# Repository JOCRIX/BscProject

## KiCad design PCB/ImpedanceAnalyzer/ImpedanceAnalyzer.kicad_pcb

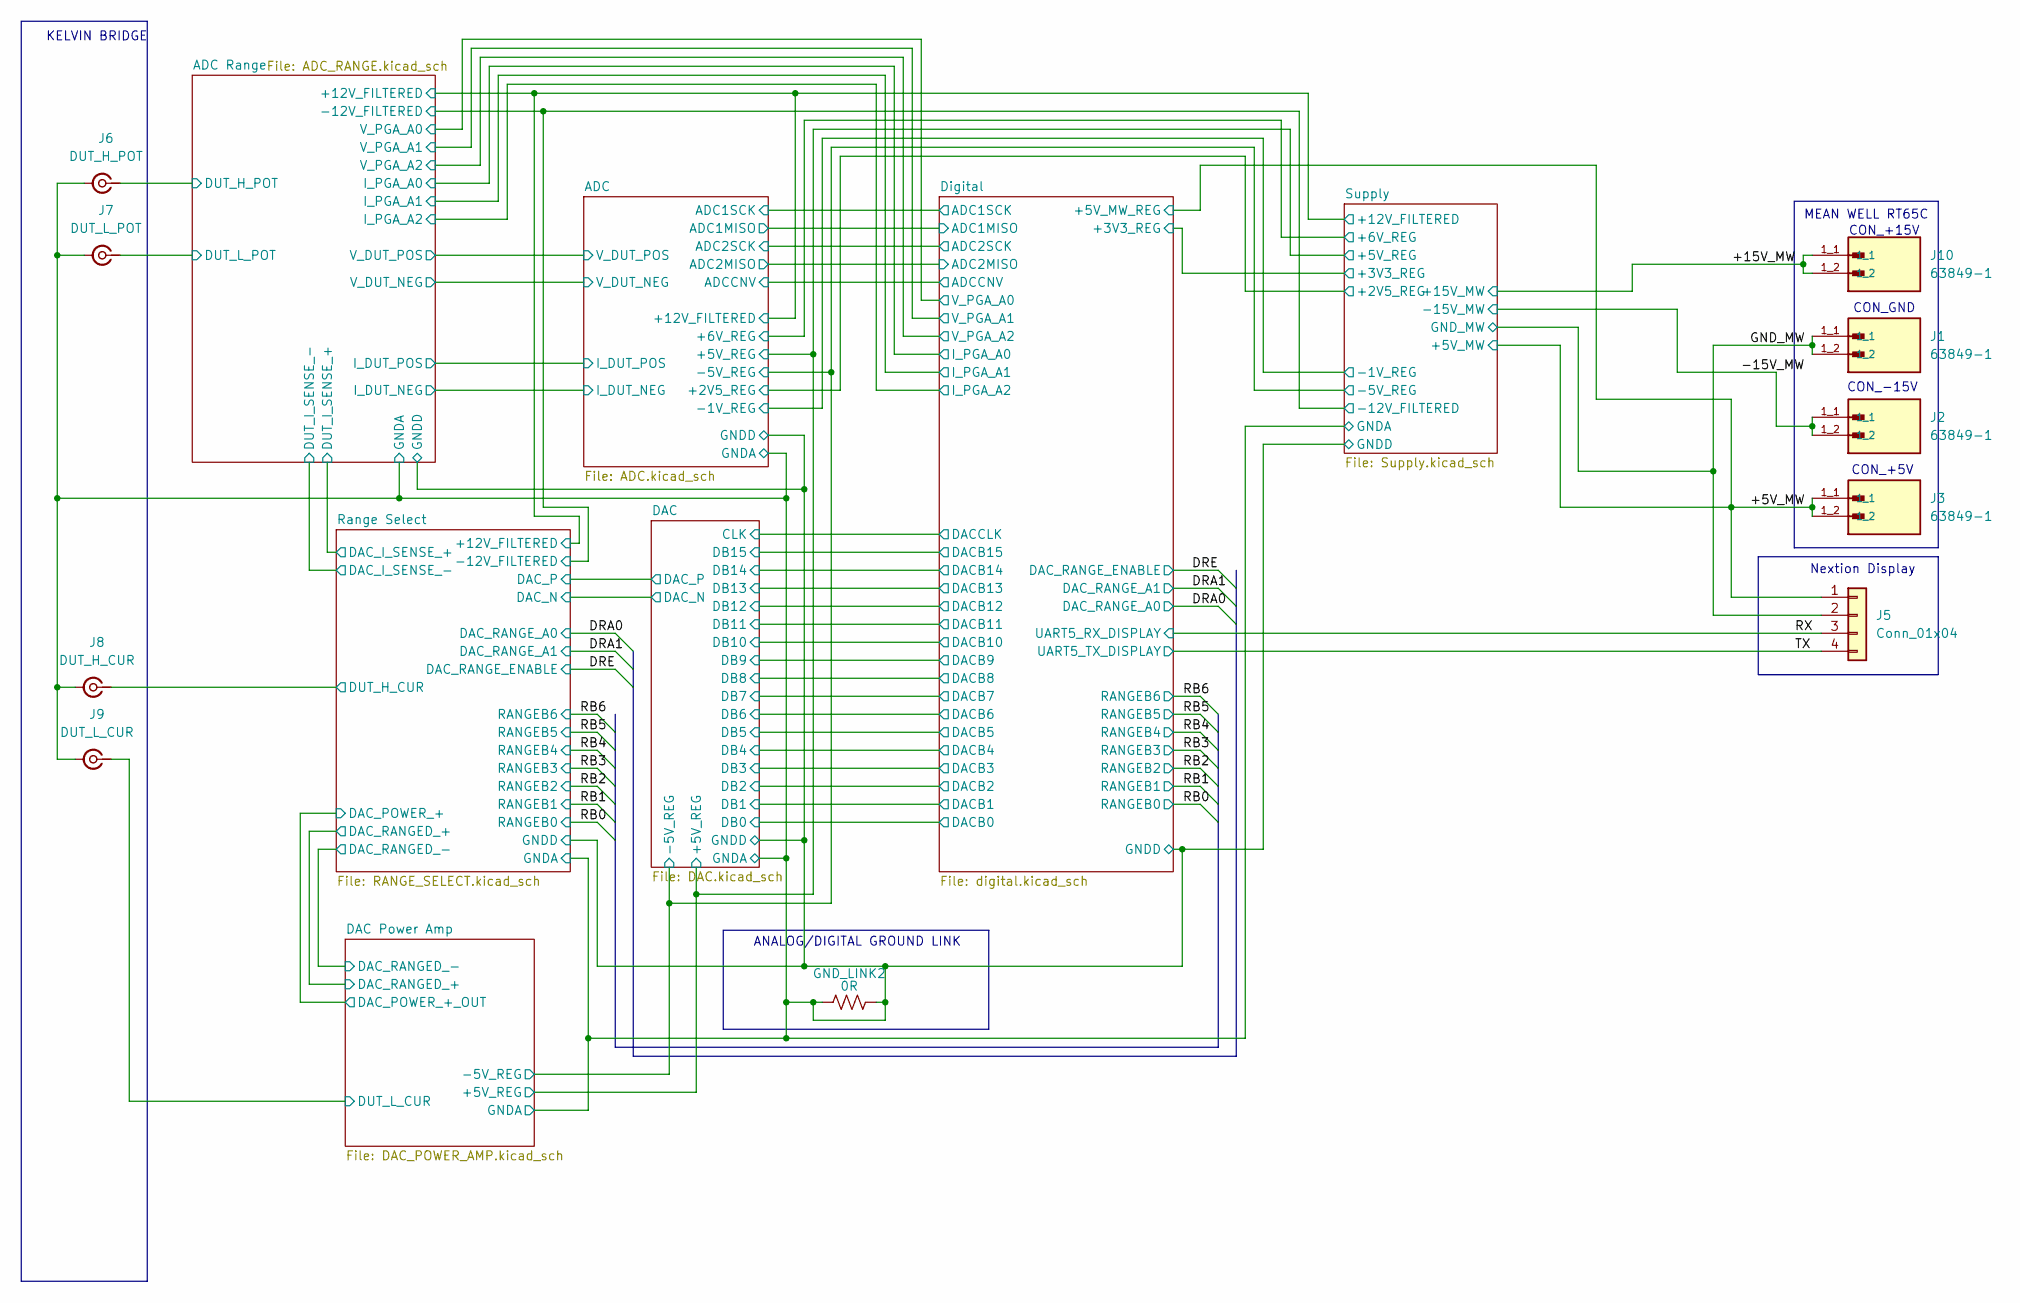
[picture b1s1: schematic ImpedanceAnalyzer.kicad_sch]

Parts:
GND_LINK2: 0R; Resistor SMD - 2818
J1, J2, J3, J10: 63849-1; TE_63849-1
J5: Conn_01x04; JST_XH_B4B-XH-A_1x04_P2.50mm_Vertical
J6: DUT_H_POT; BNC_TEConnectivity_1478204_Vertical
J7: DUT_L_POT; BNC_TEConnectivity_1478204_Vertical
J8: DUT_H_CUR; BNC_TEConnectivity_1478204_Vertical
J9: DUT_L_CUR; BNC_TEConnectivity_1478204_Vertical

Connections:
/+5V_MW: J3.1_1, J3.1_2, J5.1; also elsewhere on the board
/+15V_MW: J10.1_1, J10.1_2; also elsewhere on the board
/-15V_MW: J2.1_1, J2.1_2; also elsewhere on the board
/ADC Range/DUT_H_POT: J6.1 (In); also elsewhere on the board
/ADC Range/DUT_I_SENSE_-: J8.1 (In); also elsewhere on the board
/ADC Range/DUT_L_POT: J7.1 (In); also elsewhere on the board
/DAC Power Amp/DUT_L_CUR: J9.1 (In); also elsewhere on the board
/GND_MW: J1.1_1, J1.1_2, J5.2; also elsewhere on the board
/RX: J5.3; also elsewhere on the board
/TX: J5.4; also elsewhere on the board

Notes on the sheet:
KELVIN BRIDGE
CON_+15V
MEAN WELL RT65C
CON_GND
Nextion Display
CON_+5V
CON_-15V
ANALOG/DIGITAL GROUND LINK

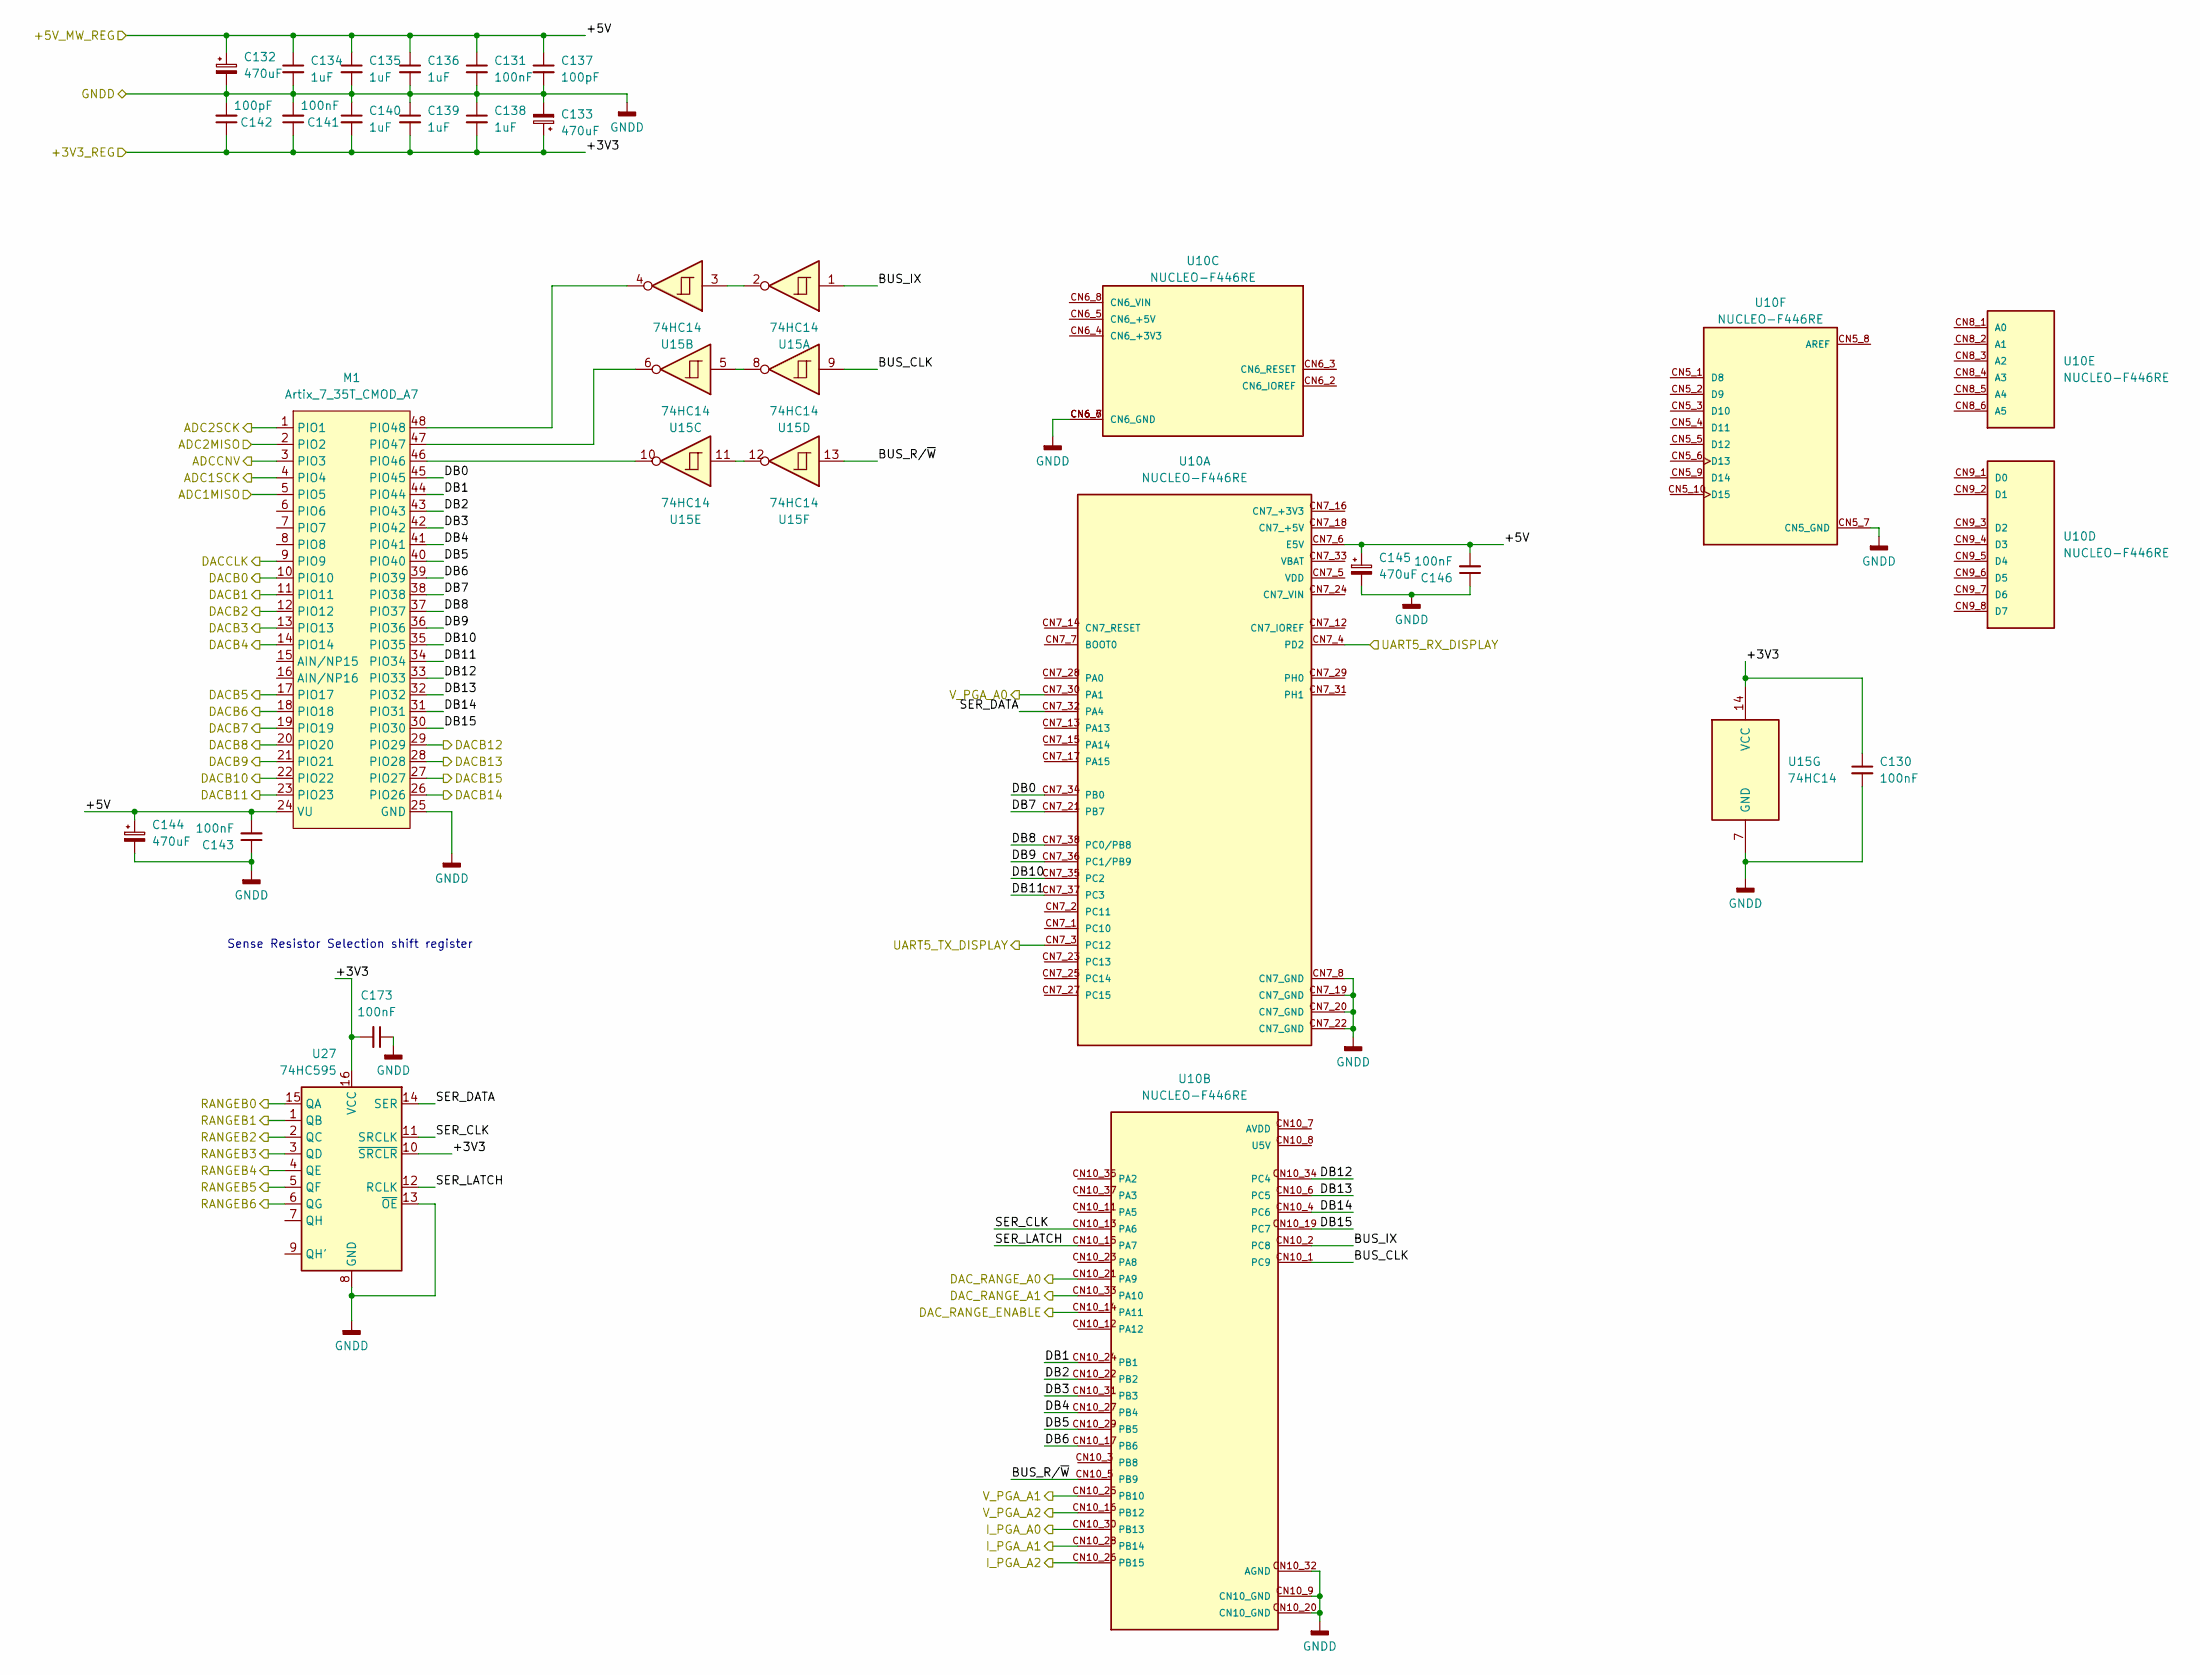
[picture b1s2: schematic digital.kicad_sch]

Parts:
C130, C131, C141, C143, C146, C173: 100nF; C_0805_2012Metric_Pad1.18x1.45mm_HandSolder
C132, C133, C144, C145: 470uF; CP_Radial_D10.0mm_P5.00mm
C134, C135, C136, C138, C139, C140: 1uF; C_0805_2012Metric_Pad1.18x1.45mm_HandSolder
C137, C142: 100pF; C_Disc_D3.4mm_W2.1mm_P2.50mm
M1: Artix_7_35T_CMOD_A7; CMOD A7 Module
U10: NUCLEO-F446RE; MODULE_NUCLEO-F446RE; PARTREV 13
U15: 74HC14; DIP-14_W7.62mm
U27: 74HC595; DIP-16_W7.62mm

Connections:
/+5V_MW: C131.1, C132.1, C134.1, C135.1, C136.1, C137.1, C143.2, C144.1, C145.1, C146.2, M1.24 (VU), U10.CN7_6 (E5V); also elsewhere on the board
/ADC Range/I_PGA_A0: U10.CN10_30 (PB13); also elsewhere on the board
/ADC Range/I_PGA_A1: U10.CN10_28 (PB14); also elsewhere on the board
/ADC Range/I_PGA_A2: U10.CN10_26 (PB15); also elsewhere on the board
/ADC Range/V_PGA_A0: U10.CN7_30 (PA1); also elsewhere on the board
/ADC Range/V_PGA_A1: U10.CN10_25 (PB10); also elsewhere on the board
/ADC Range/V_PGA_A2: U10.CN10_16 (PB12); also elsewhere on the board
/ADC/ADC1MISO: M1.5 (PIO5); also elsewhere on the board
/ADC/ADC1SCK: M1.4 (PIO4); also elsewhere on the board
/ADC/ADC2MISO: M1.2 (PIO2); also elsewhere on the board
/ADC/ADC2SCK: M1.1 (PIO1); also elsewhere on the board
/ADC/ADCCNV: M1.3 (PIO3); also elsewhere on the board
/DAC/CLK: M1.9 (PIO9); also elsewhere on the board
/DAC/DB0: M1.10 (PIO10); also elsewhere on the board
/DAC/DB1: M1.11 (PIO11); also elsewhere on the board
/DAC/DB2: M1.12 (PIO12); also elsewhere on the board
/DAC/DB3: M1.13 (PIO13); also elsewhere on the board
/DAC/DB4: M1.14 (PIO14); also elsewhere on the board
/DAC/DB5: M1.17 (PIO17); also elsewhere on the board
/DAC/DB6: M1.18 (PIO18); also elsewhere on the board
/DAC/DB7: M1.19 (PIO19); also elsewhere on the board
/DAC/DB8: M1.20 (PIO20); also elsewhere on the board
/DAC/DB9: M1.21 (PIO21); also elsewhere on the board
/DAC/DB10: M1.22 (PIO22); also elsewhere on the board
/DAC/DB11: M1.23 (PIO23); also elsewhere on the board
/DAC/DB12: M1.29 (PIO29); also elsewhere on the board
/DAC/DB13: M1.28 (PIO28); also elsewhere on the board
/DAC/DB14: M1.26 (PIO26); also elsewhere on the board
/DAC/DB15: M1.27 (PIO27); also elsewhere on the board
/DRA0: U10.CN10_21 (PA9); also elsewhere on the board
/DRA1: U10.CN10_33 (PA10); also elsewhere on the board
/DRE: U10.CN10_14 (PA11); also elsewhere on the board
/Digital/+3V3: C130.1, C133.1, C138.2, C139.2, C140.2, C141.1, C142.1, C173.2, U15.14 (VCC), U27.10 (~SRCLR), U27.16 (VCC); also elsewhere on the board
/Digital/BUS_CLK: U10.CN10_1 (PC9), U15.9
/Digital/BUS_IX: U10.CN10_2 (PC8), U15.1
/Digital/BUS_R/~W: U10.CN10_5 (PB9), U15.13
/Digital/DB0: M1.45 (PIO45), U10.CN7_34 (PB0)
/Digital/DB1: M1.44 (PIO44), U10.CN10_24 (PB1)
/Digital/DB2: M1.43 (PIO43), U10.CN10_22 (PB2)
/Digital/DB3: M1.42 (PIO42), U10.CN10_31 (PB3)
/Digital/DB4: M1.41 (PIO41), U10.CN10_27 (PB4)
/Digital/DB5: M1.40 (PIO40), U10.CN10_29 (PB5)
/Digital/DB6: M1.39 (PIO39), U10.CN10_17 (PB6)
/Digital/DB7: M1.38 (PIO38), U10.CN7_21 (PB7)
/Digital/DB8: M1.37 (PIO37), U10.CN7_38 (PC0/PB8)
/Digital/DB9: M1.36 (PIO36), U10.CN7_36 (PC1/PB9)
/Digital/DB10: M1.35 (PIO35), U10.CN7_35 (PC2)
/Digital/DB11: M1.34 (PIO34), U10.CN7_37 (PC3)
/Digital/DB12: M1.33 (PIO33), U10.CN10_34 (PC4)
/Digital/DB13: M1.32 (PIO32), U10.CN10_6 (PC5)
/Digital/DB14: M1.31 (PIO31), U10.CN10_4 (PC6)
/Digital/DB15: M1.30 (PIO30), U10.CN10_19 (PC7)
/Digital/SER_CLK: U10.CN10_13 (PA6), U27.11 (SRCLK)
/Digital/SER_DATA: U10.CN7_32 (PA4), U27.14 (SER)
/Digital/SER_LATCH: U10.CN10_15 (PA7), U27.12 (RCLK)
/RB0: U27.15 (QA); also elsewhere on the board
/RB1: U27.1 (QB); also elsewhere on the board
/RB2: U27.2 (QC); also elsewhere on the board
/RB3: U27.3 (QD); also elsewhere on the board
/RB4: U27.4 (QE); also elsewhere on the board
/RB5: U27.5 (QF); also elsewhere on the board
/RB6: U27.6 (QG); also elsewhere on the board
/RX: U10.CN7_4 (PD2); also elsewhere on the board
/TX: U10.CN7_3 (PC12); also elsewhere on the board
unnamed: M1.46 (PIO46), U15.10
unnamed: M1.47 (PIO47), U15.6
unnamed: M1.48 (PIO48), U15.4
unnamed: U15.2, U15.3
unnamed: U15.5, U15.8
unnamed: U15.11, U15.12

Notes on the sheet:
Sense Resistor Selection shift register

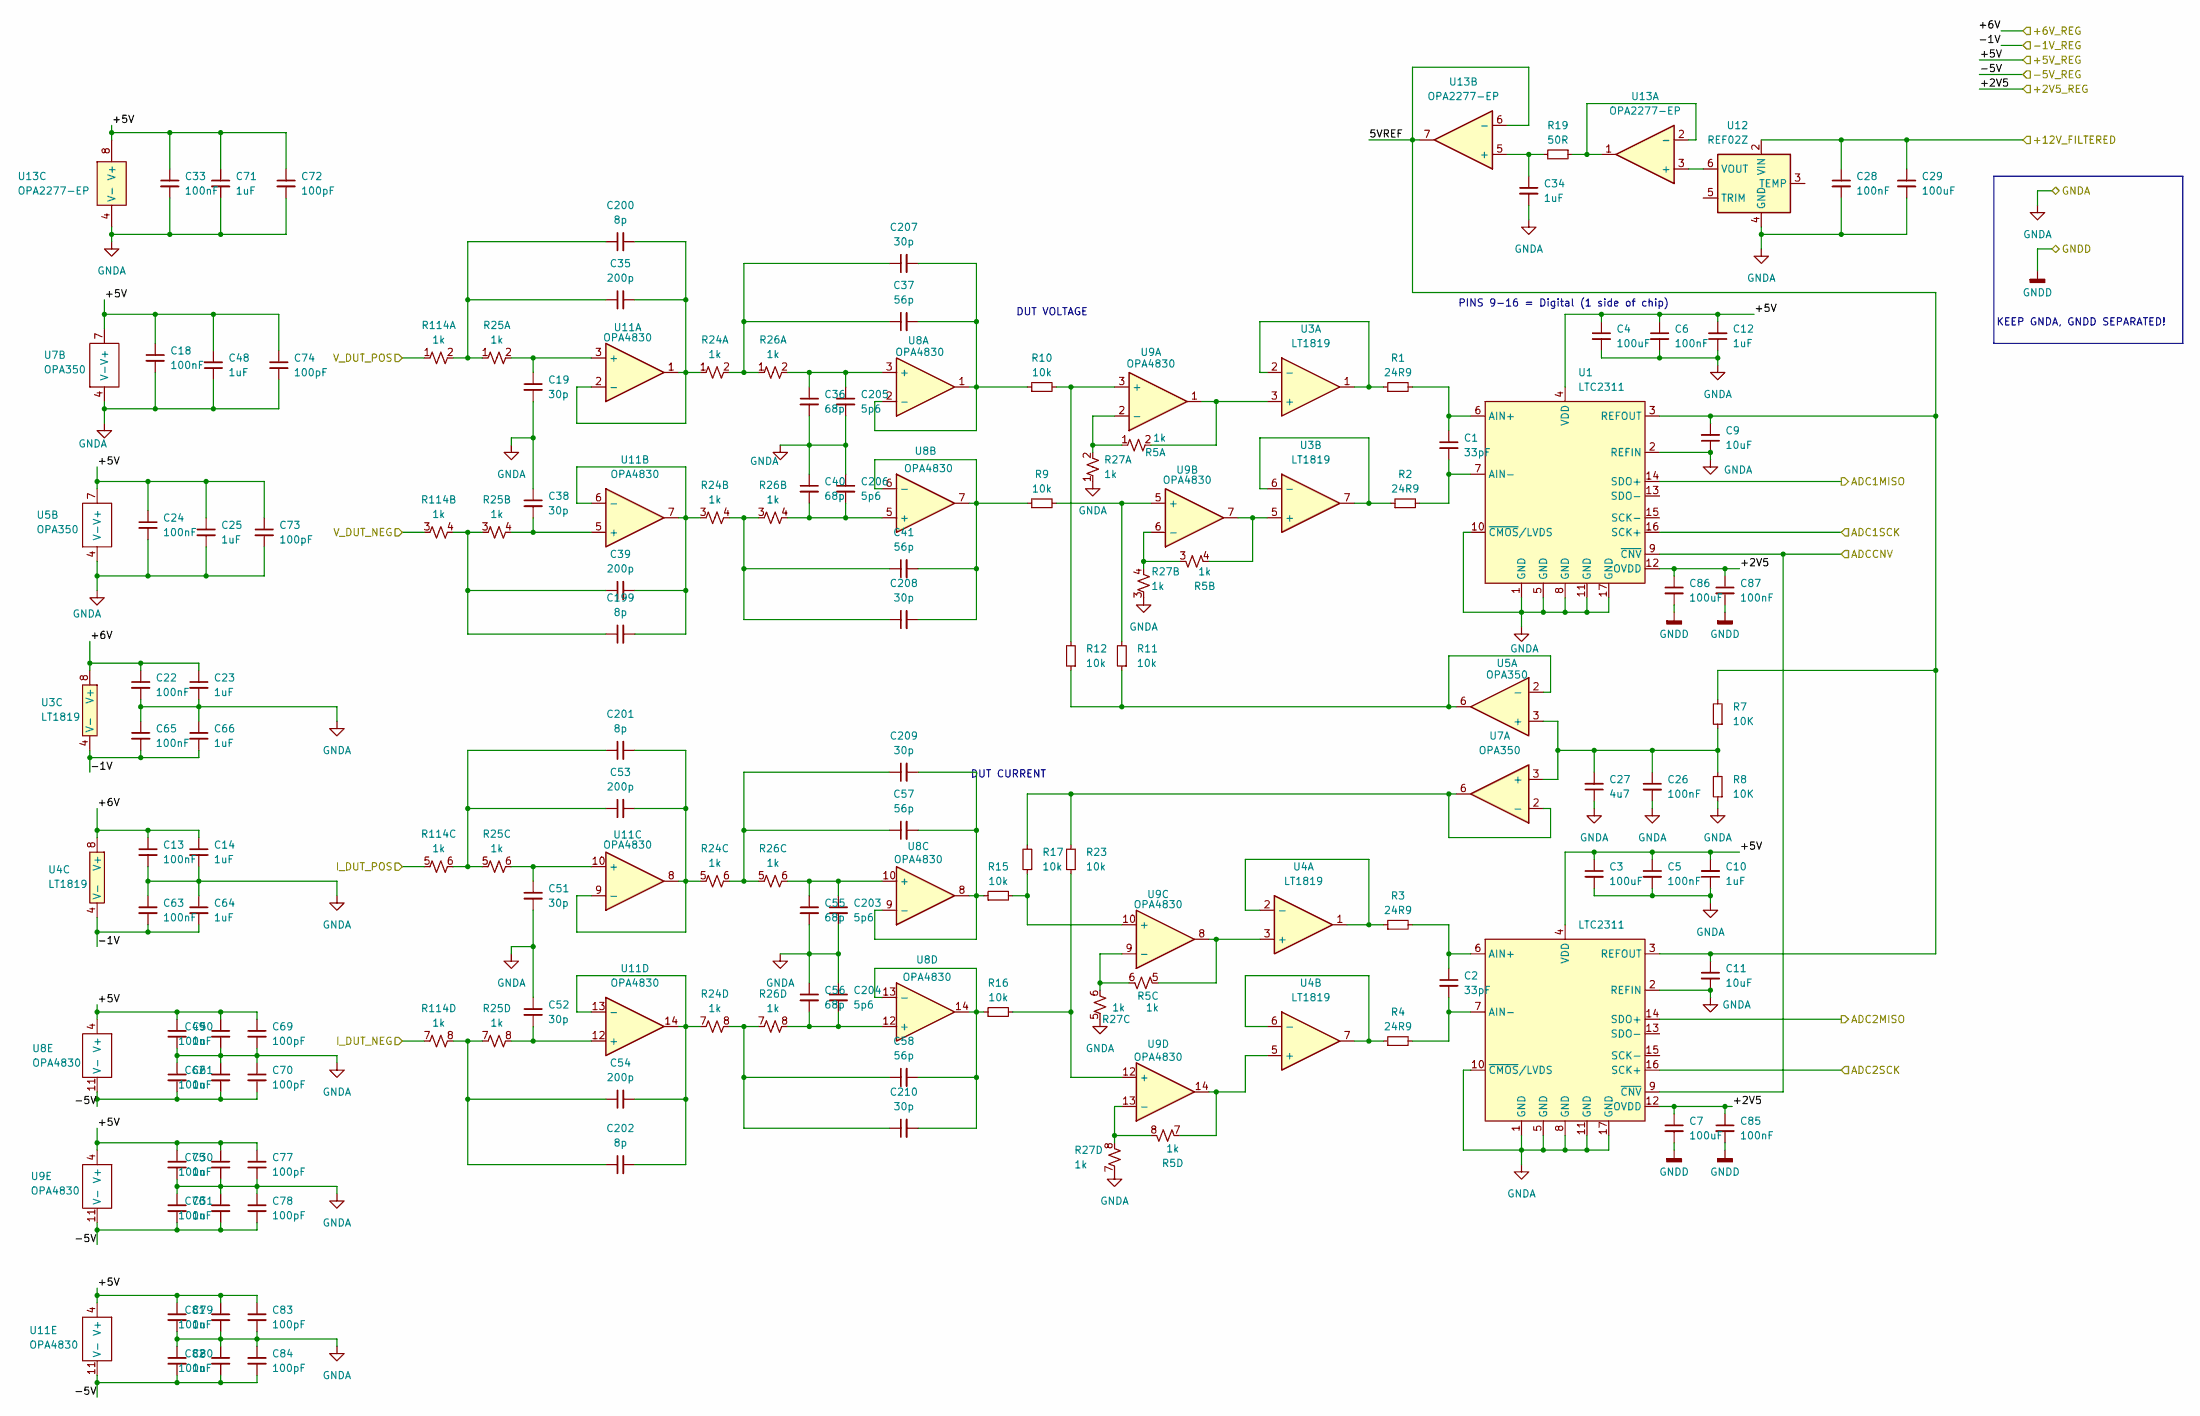
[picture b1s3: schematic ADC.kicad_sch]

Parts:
C1, C2: 33pF; C_0805_2012Metric_Pad1.18x1.45mm_HandSolder
C3, C4, C7, C29, C86: 100uF; C_1206_3216Metric_Pad1.33x1.80mm_HandSolder
C5, C6, C13, C18, C22, C24, C26, C28, C33, C63, C65, C85, C87: 100nF; C_0805_2012Metric_Pad1.18x1.45mm_HandSolder
C9, C11: 10uF; C_1206_3216Metric_Pad1.33x1.80mm_HandSolder
C10, C12, C14, C23, C25, C30, C31, C34, C48, C50, C61, C64, C66, C71, C79, C80: 1uF; C_0805_2012Metric_Pad1.18x1.45mm_HandSolder
C19, C38, C51, C52, C207, C208, C209, C210: 30p; C_0603_1608Metric_Pad1.08x0.95mm_HandSolder
C27: 4u7; C_1206_3216Metric_Pad1.33x1.80mm_HandSolder
C35, C39, C53, C54: 200p; C_0603_1608Metric_Pad1.08x0.95mm_HandSolder
C36, C40, C55, C56: 68p; C_0603_1608Metric_Pad1.08x0.95mm_HandSolder
C37, C41, C57, C58: 56p; C_0603_1608Metric_Pad1.08x0.95mm_HandSolder
C49, C62, C75, C76, C81, C82: 100n; C_0805_2012Metric_Pad1.18x1.45mm_HandSolder
C69, C70, C72, C73, C74, C77, C78, C83, C84: 100pF; C_Disc_D3.4mm_W2.1mm_P2.50mm
C199, C200, C201, C202: 8p; C_0603_1608Metric_Pad1.08x0.95mm_HandSolder
C203, C204, C205, C206: 5p6; C_0603_1608Metric_Pad1.08x0.95mm_HandSolder
R1, R2, R3, R4: 24R9; R_0805_2012Metric_Pad1.20x1.40mm_HandSolder
R5, R24, R25, R26, R27, R114: 1k; R_Array_SIP8
R7, R8: 10K; R_0805_2012Metric_Pad1.20x1.40mm_HandSolder
R9, R10, R11, R12, R15, R16, R17, R23: 10k; R_0805_2012Metric_Pad1.20x1.40mm_HandSolder
R19: 50R; R_0805_2012Metric_Pad1.20x1.40mm_HandSolder
U1, U2: LTC2311; MSOP-16-1EP_3x4mm_P0.5mm_EP1.65x2.85mm_ThermalVias
U3, U4: LT1819; SOIC-8_3.9x4.9mm_P1.27mm
U5, U7: OPA350; DIP-8_W7.62mm
U8, U9, U11: OPA4830; TSSOP-14_4.4x5mm_P0.65mm
U12: REF02Z; DIP-8_W7.62mm
U13: OPA2277-EP; DIP-8_W7.62mm

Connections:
/ADC Range/+12V: C28.1, C29.1, U12.2 (VIN); also elsewhere on the board
/ADC Range/I_DUT_NEG: R114.7; also elsewhere on the board
/ADC Range/I_DUT_POS: R114.5; also elsewhere on the board
/ADC Range/V_DUT_NEG: R114.3; also elsewhere on the board
/ADC Range/V_DUT_POS: R114.1; also elsewhere on the board
/ADC/5VREF: C9.2, C11.1, R7.2, U1.3 (REFOUT), U2.3 (REFOUT), U13.6 (-), U13.7
/ADC/+2V5: C7.1, C85.1, C86.1, C87.1, U1.12 (OVDD), U2.12 (OVDD); also elsewhere on the board
/ADC/+6V: C13.1, C14.1, C22.1, C23.1, U3.8 (V+), U4.8 (V+); also elsewhere on the board
/ADC/-1V: C63.2, C64.2, C65.2, C66.2, U3.4 (V-), U4.4 (V-); also elsewhere on the board
/ADC/ADC1MISO: U1.14 (SDO+); also elsewhere on the board
/ADC/ADC1SCK: U1.16 (SCK+); also elsewhere on the board
/ADC/ADC2MISO: U2.14 (SDO+); also elsewhere on the board
/ADC/ADC2SCK: U2.16 (SCK+); also elsewhere on the board
/ADC/ADCCNV: U1.9 (~CNV), U2.9 (~CNV); also elsewhere on the board
unnamed: C39.1, C199.1, R25.3, R114.4
unnamed: C35.1, C200.1, R25.1, R114.2
unnamed: C53.1, C201.1, R25.5, R114.6
unnamed: C54.1, C202.1, R25.7, R114.8
unnamed: C37.1, C207.1, R24.2, R26.1
unnamed: C41.1, C208.1, R24.4, R26.3
unnamed: C57.1, C209.1, R24.6, R26.5
unnamed: C58.1, C210.1, R24.8, R26.7
unnamed: C1.1, R1.2, U1.6 (AIN+)
unnamed: C1.2, R2.2, U1.7 (AIN-)
unnamed: C2.1, R3.2, U2.6 (AIN+)
unnamed: C2.2, R4.2, U2.7 (AIN-)
unnamed: R5.2, U3.3 (+), U9.1
unnamed: R1.1, U3.1, U3.2 (-)
unnamed: R5.4, U3.5 (+), U9.7
unnamed: R2.1, U3.6 (-), U3.7
unnamed: R5.5, U4.3 (+), U9.8
unnamed: R3.1, U4.1, U4.2 (-)
unnamed: R5.7, U4.5 (+), U9.14
unnamed: R4.1, U4.6 (-), U4.7
unnamed: C26.1, C27.2, R7.1, R8.2, U5.3 (+), U7.3 (+)
unnamed: R11.1, R12.1, U5.2 (-), U5.6
unnamed: R17.2, R23.2, U7.2 (-), U7.6
unnamed: C36.1, C205.1, R26.2, U8.3 (+)
unnamed: C37.2, C207.2, R10.1, U8.1, U8.2 (-)
unnamed: C40.2, C206.2, R26.4, U8.5 (+)
unnamed: C41.2, C208.2, R9.1, U8.6 (-), U8.7
unnamed: C55.1, C203.1, R26.6, U8.10 (+)
unnamed: C57.2, C209.2, R15.1, U8.8, U8.9 (-)
unnamed: C56.2, C204.2, R26.8, U8.12 (+)
unnamed: C58.2, C210.2, R16.1, U8.13 (-), U8.14
unnamed: R10.2, R12.2, U9.3 (+)
unnamed: R5.1, R27.2, U9.2 (-)
unnamed: R9.2, R11.2, U9.5 (+)
unnamed: R5.3, R27.4, U9.6 (-)
unnamed: R15.2, R17.1, U9.10 (+)
unnamed: R5.6, R27.6, U9.9 (-)
unnamed: R16.2, R23.1, U9.12 (+)
unnamed: R5.8, R27.8, U9.13 (-)
unnamed: C19.1, R25.2, U11.3 (+)
unnamed: C35.2, C200.2, R24.1, U11.1, U11.2 (-)
unnamed: C38.2, R25.4, U11.5 (+)
unnamed: C39.2, C199.2, R24.3, U11.6 (-), U11.7
unnamed: C51.1, R25.6, U11.10 (+)
unnamed: C53.2, C201.2, R24.5, U11.8, U11.9 (-)
unnamed: C52.2, R25.8, U11.12 (+)
unnamed: C54.2, C202.2, R24.7, U11.13 (-), U11.14
unnamed: U12.6 (VOUT), U13.3 (+)
unnamed: R19.1, U13.1, U13.2 (-)
unnamed: C34.1, R19.2, U13.5 (+)

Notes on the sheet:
KEEP GNDA, GNDD SEPARATED!
DUT CURRENT
PINS 9-16 = Digital (1 side of chip)
DUT VOLTAGE

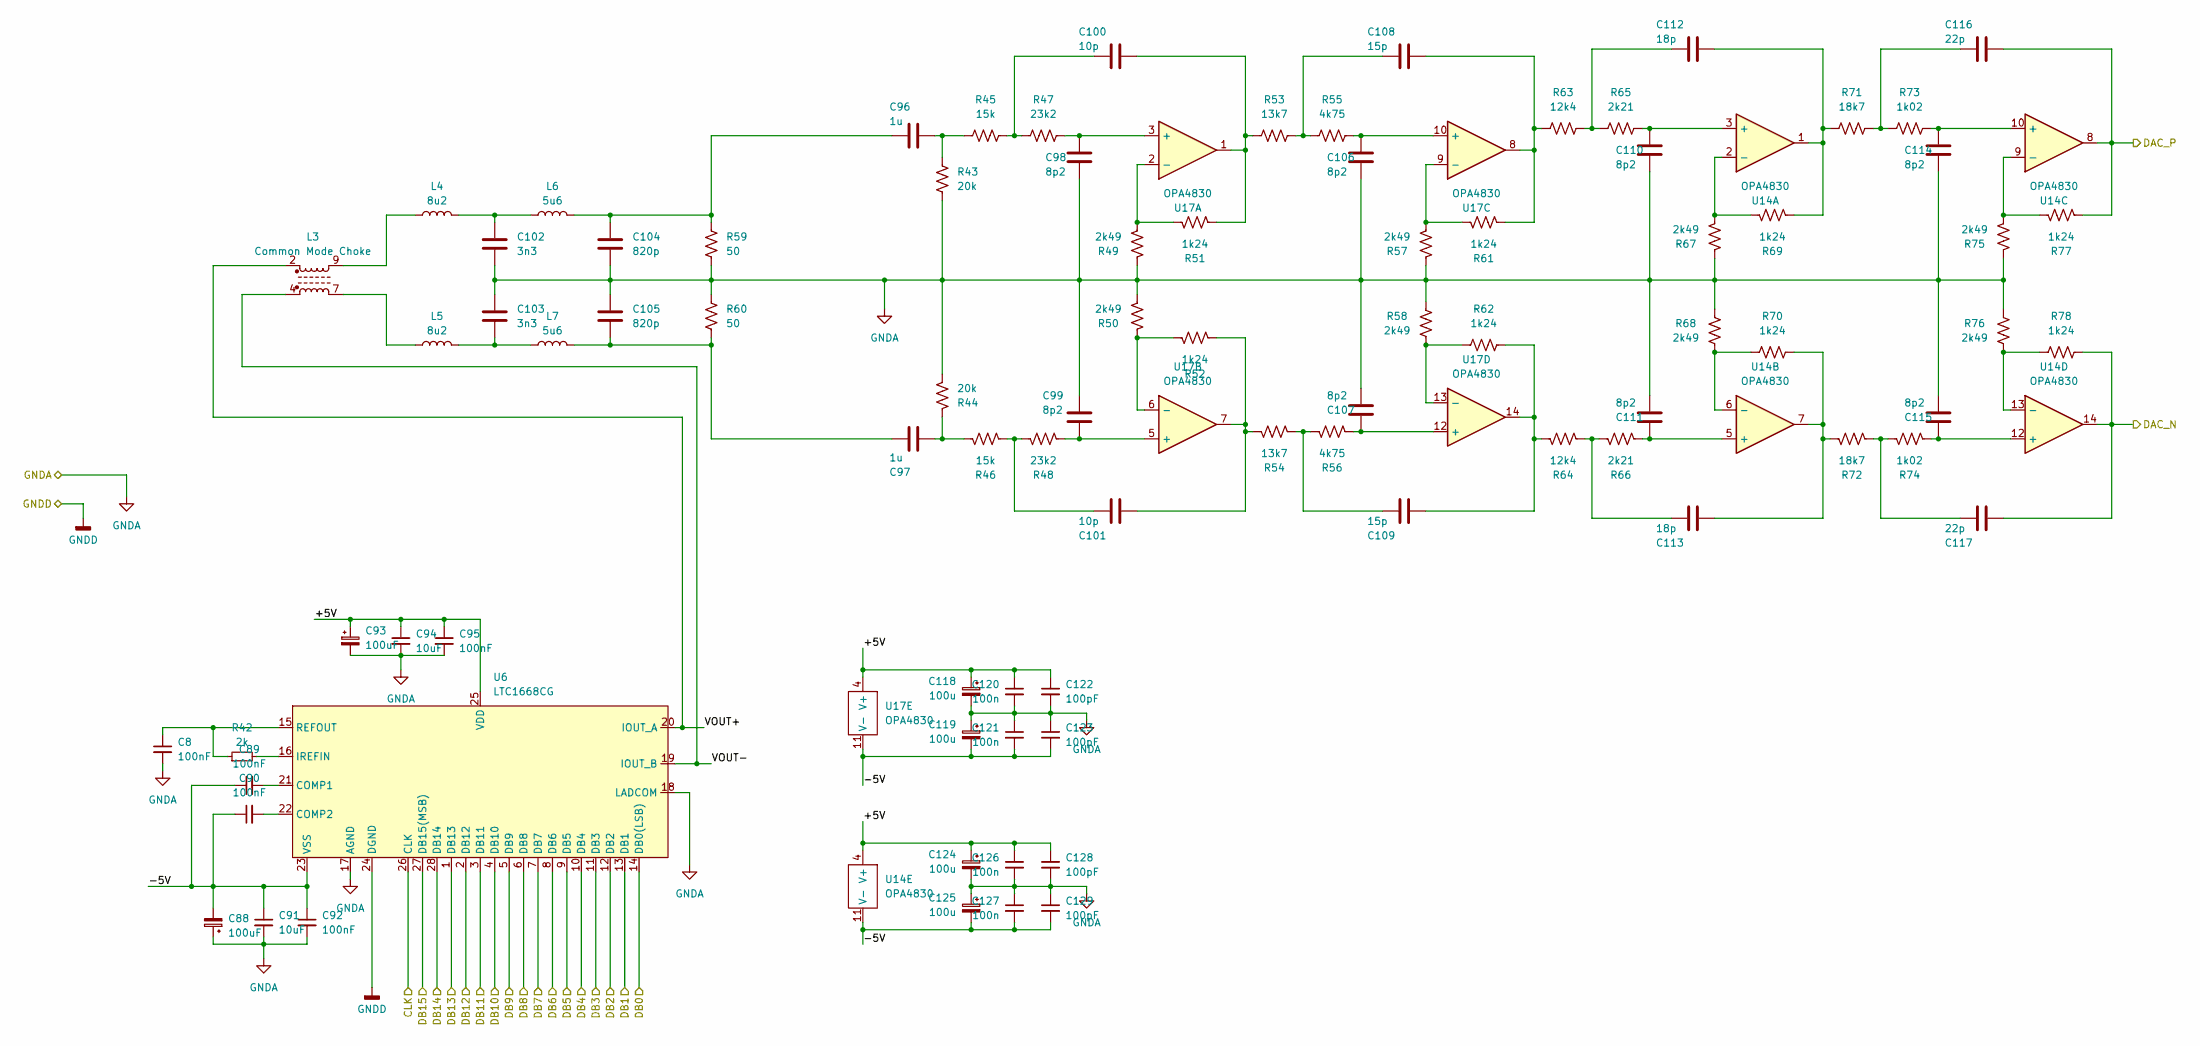
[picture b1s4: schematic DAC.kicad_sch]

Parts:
C8, C89, C90, C92, C95: 100nF; C_0805_2012Metric_Pad1.18x1.45mm_HandSolder
C88, C93: 100uF; CP_Radial_D6.3mm_P2.50mm
C91, C94: 10uF; C_1206_3216Metric_Pad1.33x1.80mm_HandSolder
C96, C97: 1u; C_0805_2012Metric_Pad1.18x1.45mm_HandSolder
C98, C99, C106, C107, C110, C111, C114, C115: 8p2; C_Disc_D3.4mm_W2.1mm_P2.50mm
C100, C101: 10p; C_Disc_D3.0mm_W2.0mm_P2.50mm
C102, C103: 3n3; C_Disc_D4.7mm_W2.5mm_P5.00mm
C104, C105: 820p; C_Disc_D4.7mm_W2.5mm_P5.00mm
C108, C109: 15p; C_Disc_D3.4mm_W2.1mm_P2.50mm
C112, C113: 18p; C_Disc_D3.4mm_W2.1mm_P2.50mm
C116, C117: 22p; C_Disc_D3.4mm_W2.1mm_P2.50mm
C118, C119, C124, C125: 100u; CP_Radial_D6.3mm_P2.50mm
C120, C121, C126, C127: 100n; C_0805_2012Metric_Pad1.18x1.45mm_HandSolder
C122, C123, C128, C129: 100pF; C_Disc_D3.4mm_W2.1mm_P2.50mm
L3: Common Mode Choke; L_CommonMode_Wuerth_WE-CMB-L
L4, L5: 8u2; L_Axial_L14.5mm_D5.8mm_P20.32mm_Horizontal_Fastron_HBCC
L6, L7: 5u6; L_Axial_L9.5mm_D4.0mm_P12.70mm_Horizontal_Fastron_SMCC
R42: 2k; R_0805_2012Metric_Pad1.20x1.40mm_HandSolder
R43, R44: 20k; R_Axial_DIN0207_L6.3mm_D2.5mm_P10.16mm_Horizontal
R45, R46: 15k; R_Axial_DIN0207_L6.3mm_D2.5mm_P10.16mm_Horizontal
R47, R48: 23k2; R_Axial_DIN0207_L6.3mm_D2.5mm_P10.16mm_Horizontal
R49, R50, R57, R58, R67, R68, R75, R76: 2k49; R_Axial_DIN0207_L6.3mm_D2.5mm_P10.16mm_Horizontal
R51, R52, R61, R62, R69, R70, R77, R78: 1k24; R_Axial_DIN0207_L6.3mm_D2.5mm_P10.16mm_Horizontal
R53, R54: 13k7; R_Axial_DIN0207_L6.3mm_D2.5mm_P10.16mm_Horizontal
R55, R56: 4k75; R_Axial_DIN0207_L6.3mm_D2.5mm_P10.16mm_Horizontal
R59, R60: 50; R_Axial_DIN0207_L6.3mm_D2.5mm_P10.16mm_Horizontal
R63, R64: 12k4; R_Axial_DIN0207_L6.3mm_D2.5mm_P10.16mm_Horizontal
R65, R66: 2k21; R_Axial_DIN0207_L6.3mm_D2.5mm_P10.16mm_Horizontal
R71, R72: 18k7; R_Axial_DIN0207_L6.3mm_D2.5mm_P10.16mm_Horizontal
R73, R74: 1k02; R_Axial_DIN0207_L6.3mm_D2.5mm_P10.16mm_Horizontal
U6: LTC1668CG; SSOP-28_5.3x10.2mm_P0.65mm
U14, U17: OPA4830; TSSOP-14_4.4x5mm_P0.65mm

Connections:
/DAC/CLK: U6.26 (CLK); also elsewhere on the board
/DAC/DAC_N: C117.2, R78.1, U14.14; also elsewhere on the board
/DAC/DAC_P: C116.2, R77.1, U14.8; also elsewhere on the board
/DAC/DB0: U6.14 (DB0(LSB)); also elsewhere on the board
/DAC/DB1: U6.13 (DB1); also elsewhere on the board
/DAC/DB2: U6.12 (DB2); also elsewhere on the board
/DAC/DB3: U6.11 (DB3); also elsewhere on the board
/DAC/DB4: U6.10 (DB4); also elsewhere on the board
/DAC/DB5: U6.9 (DB5); also elsewhere on the board
/DAC/DB6: U6.8 (DB6); also elsewhere on the board
/DAC/DB7: U6.7 (DB7); also elsewhere on the board
/DAC/DB8: U6.6 (DB8); also elsewhere on the board
/DAC/DB9: U6.5 (DB9); also elsewhere on the board
/DAC/DB10: U6.4 (DB10); also elsewhere on the board
/DAC/DB11: U6.3 (DB11); also elsewhere on the board
/DAC/DB12: U6.2 (DB12); also elsewhere on the board
/DAC/DB13: U6.1 (DB13); also elsewhere on the board
/DAC/DB14: U6.28 (DB14); also elsewhere on the board
/DAC/DB15: U6.27 (DB15(MSB)); also elsewhere on the board
/DAC/VOUT+: L3.2 (1), U6.20 (IOUT_A)
/DAC/VOUT-: L3.4 (2), U6.19 (IOUT_B)
unnamed: C96.2, R43.2, R45.1
unnamed: C97.2, R44.2, R46.1
unnamed: C100.1, R45.2, R47.1
unnamed: C100.2, R51.1, R53.1, U17.1
unnamed: C101.1, R46.2, R48.1
unnamed: C101.2, R52.1, R54.1, U17.7
unnamed: C102.1, L4.2, L6.1
unnamed: C103.2, L5.2, L7.1
unnamed: C96.1, C104.1, L6.2, R59.1
unnamed: C97.1, C105.2, L7.2, R60.2
unnamed: C108.1, R53.2, R55.1
unnamed: C108.2, R61.1, R63.1, U17.8
unnamed: C109.1, R54.2, R56.1
unnamed: C112.1, R63.2, R65.1
unnamed: C112.2, R69.1, R71.1, U14.1
unnamed: C113.2, R70.1, R72.1, U14.7
unnamed: C116.1, R71.2, R73.1
unnamed: C117.1, R72.2, R74.1
unnamed: L3.9 (3), L4.1
unnamed: L3.7 (4), L5.1
unnamed: C89.2, U6.21 (COMP1)
unnamed: C90.2, U6.22 (COMP2)
unnamed: R42.2, U6.16 (IREFIN)
unnamed: C8.1, R42.1, U6.15 (REFOUT)
unnamed: C110.2, R65.2, U14.3 (+)
unnamed: R67.2, R69.2, U14.2 (-)
unnamed: C111.2, R66.2, U14.5 (+)
unnamed: R68.2, R70.2, U14.6 (-)
unnamed: C114.2, R73.2, U14.10 (+)
unnamed: R75.2, R77.2, U14.9 (-)
unnamed: C115.2, R74.2, U14.12 (+)
unnamed: R76.2, R78.2, U14.13 (-)
unnamed: C98.2, R47.2, U17.3 (+)
unnamed: R49.2, R51.2, U17.2 (-)
unnamed: C99.1, R48.2, U17.5 (+)
unnamed: R50.1, R52.2, U17.6 (-)
unnamed: C106.2, R55.2, U17.10 (+)
unnamed: R57.2, R61.2, U17.9 (-)
unnamed: C107.2, R56.2, U17.12 (+)
unnamed: R58.2, R62.2, U17.13 (-)

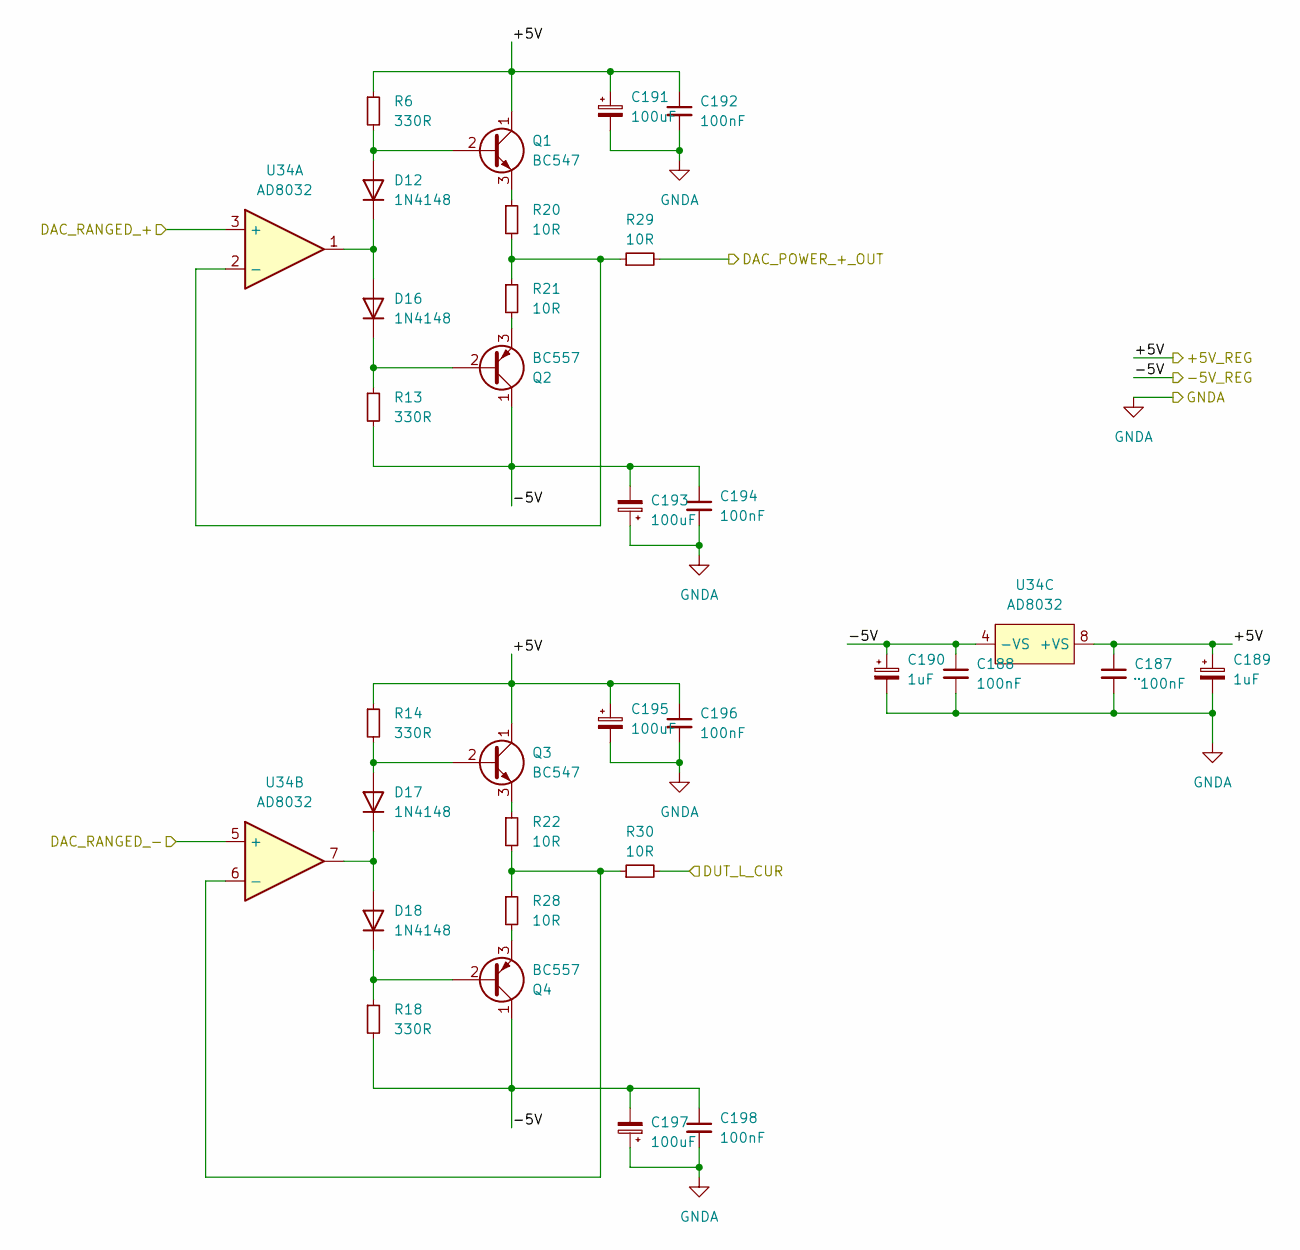
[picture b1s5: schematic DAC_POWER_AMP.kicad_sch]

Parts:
C187: ¨100nF; C_0805_2012Metric_Pad1.18x1.45mm_HandSolder
C188, C192, C194, C196, C198: 100nF; C_0805_2012Metric_Pad1.18x1.45mm_HandSolder
C189, C190: 1uF; C_0805_2012Metric_Pad1.18x1.45mm_HandSolder
C191, C193, C195, C197: 100uF; CP_Radial_D6.3mm_P2.50mm
D12, D16, D17, D18: 1N4148; D_DO-35_SOD27_P7.62mm_Horizontal
Q1, Q3: BC547; TO-92_Inline
Q2, Q4: BC557; TO-92_Inline
R6, R13, R14, R18: 330R; R_Axial_DIN0207_L6.3mm_D2.5mm_P10.16mm_Horizontal
R20, R21, R22, R28, R29, R30: 10R; R_Axial_DIN0207_L6.3mm_D2.5mm_P10.16mm_Horizontal
U34: AD8032; DIP-8_W7.62mm

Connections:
/ADC Range/DUT_I_SENSE_+: R29.2; also elsewhere on the board
/DAC Power Amp/DAC_RANGED_+: U34.3 (+); also elsewhere on the board
/DAC Power Amp/DAC_RANGED_-: U34.5 (+); also elsewhere on the board
/DAC Power Amp/DUT_L_CUR: R30.2; also elsewhere on the board
unnamed: D12.2 (A), Q1.2 (B), R6.2
unnamed: D12.1 (K), D16.2 (A), U34.1
unnamed: D16.1 (K), Q2.2 (B), R13.1
unnamed: D17.2 (A), Q3.2 (B), R14.2
unnamed: D17.1 (K), D18.2 (A), U34.7
unnamed: D18.1 (K), Q4.2 (B), R18.1
unnamed: Q1.3 (E), R20.1
unnamed: Q2.3 (E), R21.2
unnamed: Q3.3 (E), R22.1
unnamed: Q4.3 (E), R28.2
unnamed: R20.2, R21.1, R29.1, U34.2 (-)
unnamed: R22.2, R28.1, R30.1, U34.6 (-)
